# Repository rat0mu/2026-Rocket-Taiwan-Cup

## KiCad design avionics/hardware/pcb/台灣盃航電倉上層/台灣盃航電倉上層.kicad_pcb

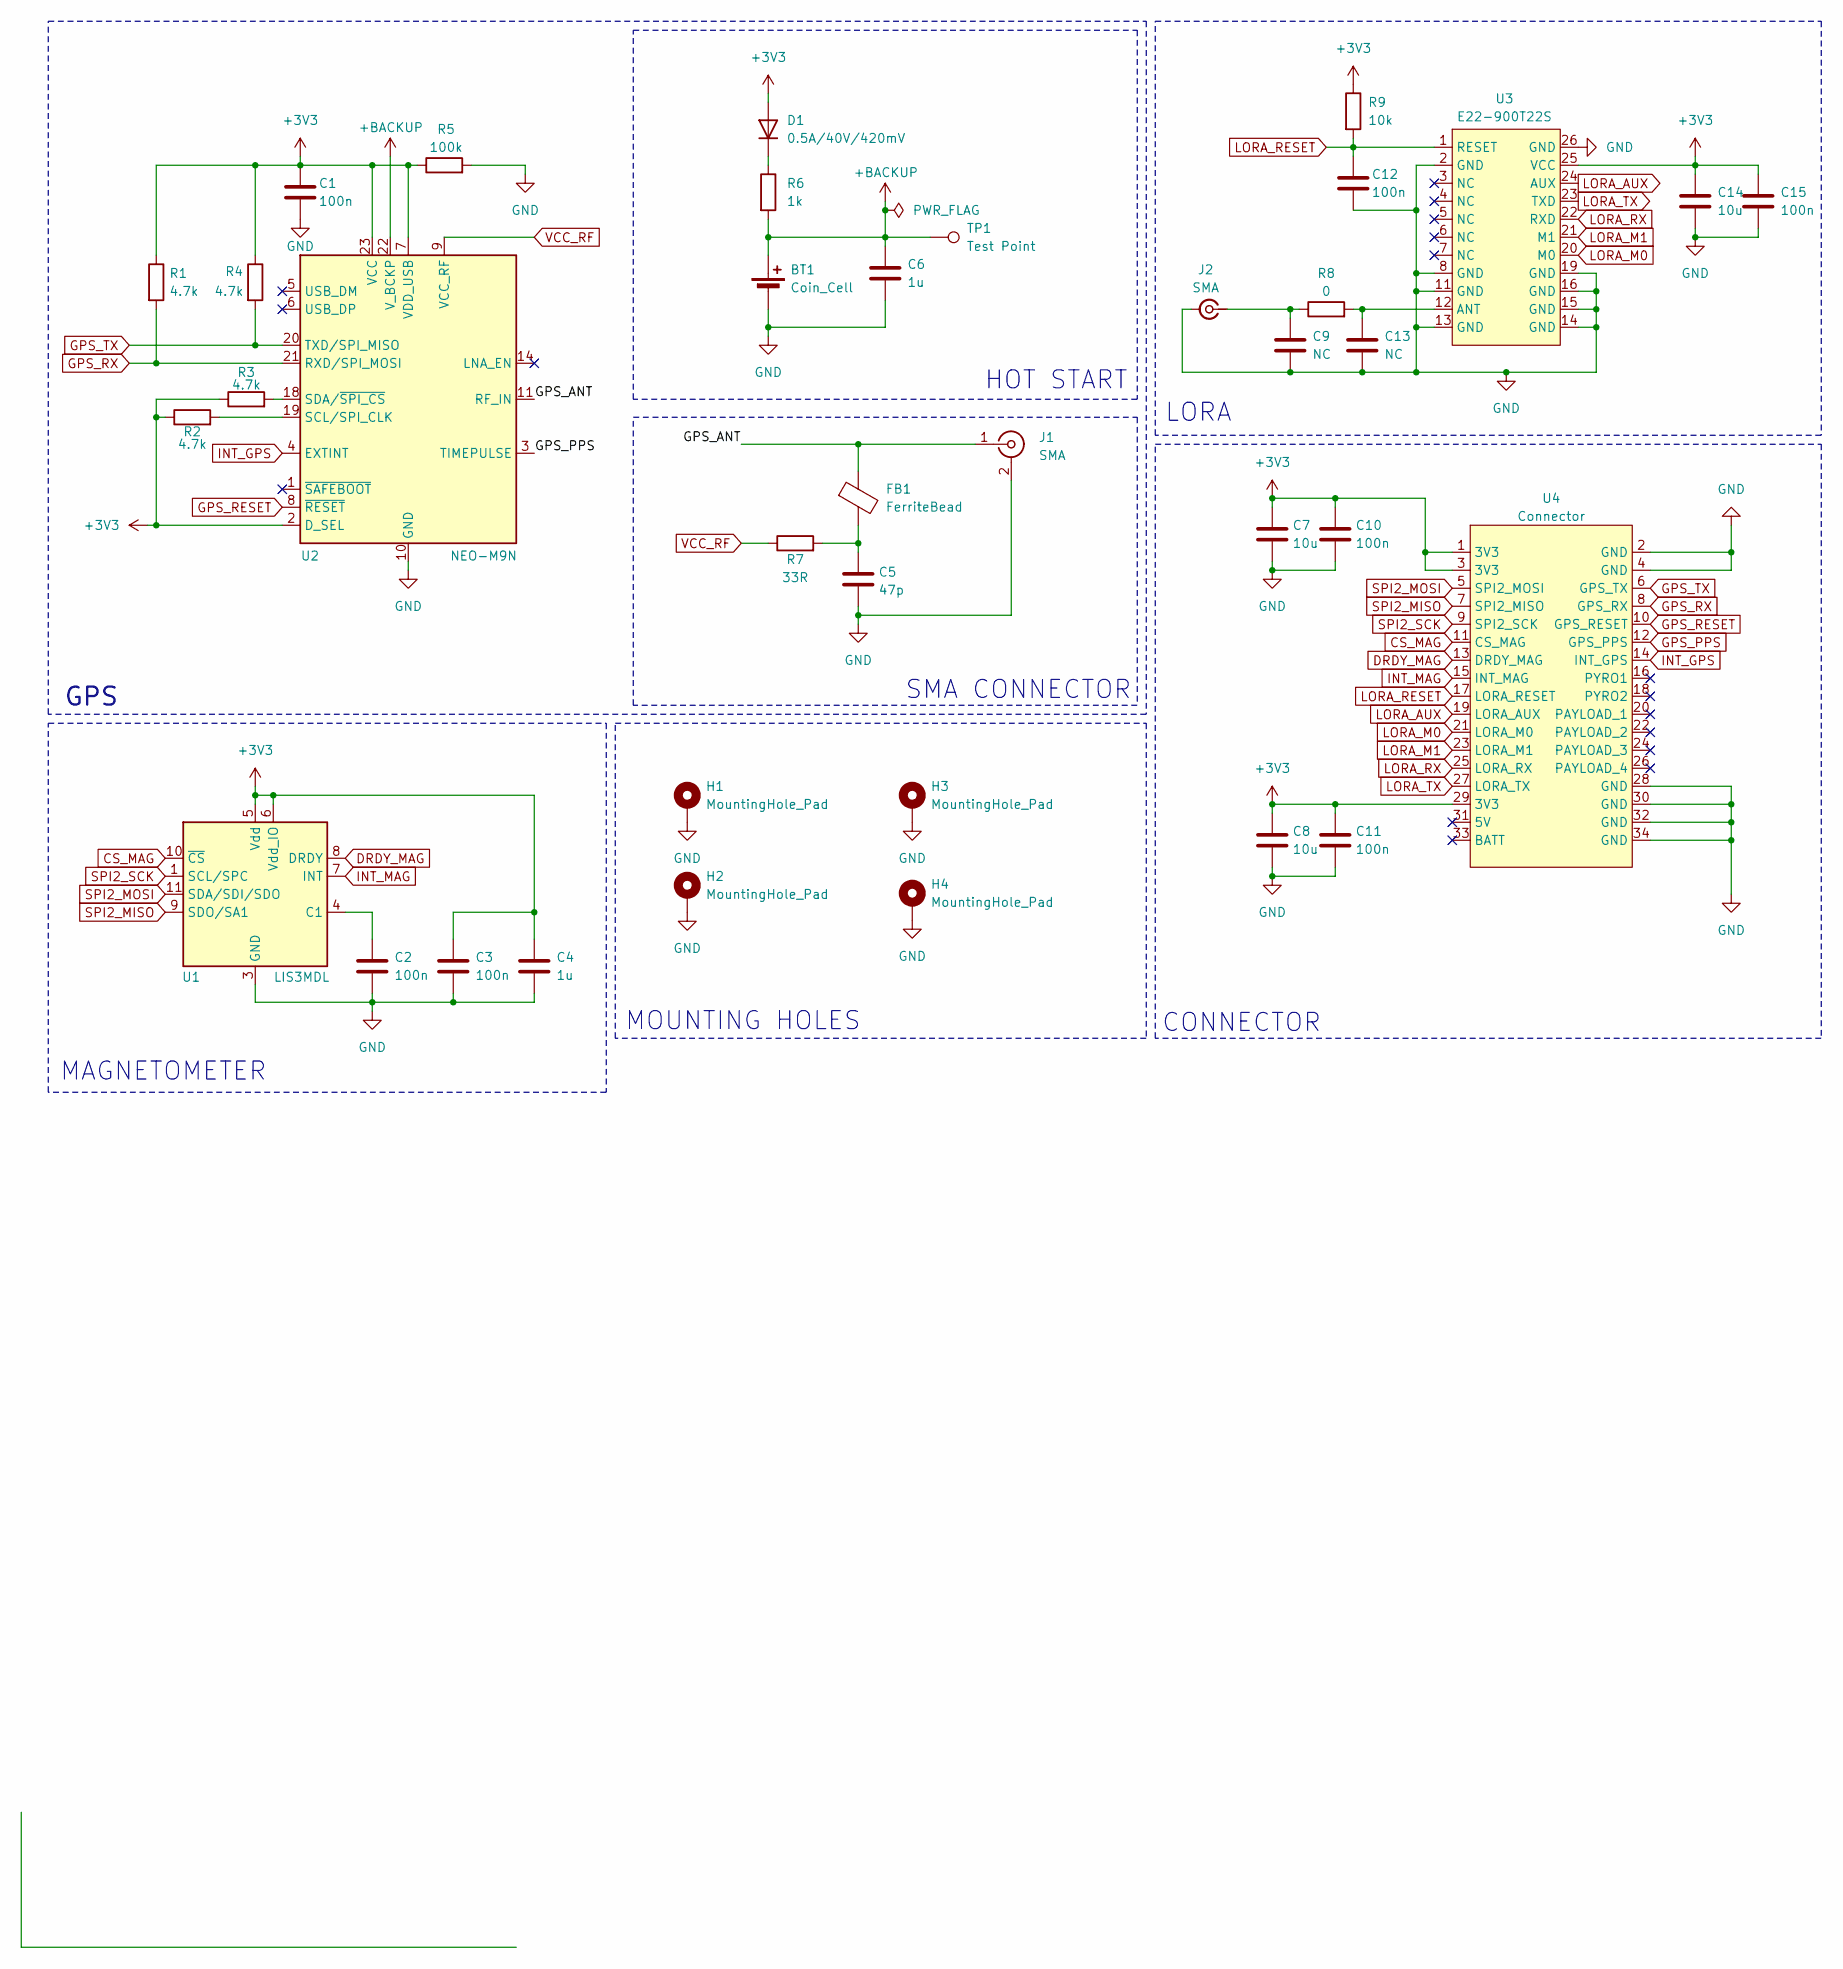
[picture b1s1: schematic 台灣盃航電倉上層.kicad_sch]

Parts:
BT1: Coin_Cell; BatteryHolder_Keystone_3000_1x12mm
C1: 100n; C_0201_0603Metric
C2, C3, C10, C11, C12, C15: 100n; C_0603_1608Metric
C4: 1u; C_0603_1608Metric
C5: 47p; C_0201_0603Metric
C6: 1u; C_0201_0603Metric
C7, C8, C14: 10u; C_0805_2012Metric
C9, C13: NC; C_0402_1005Metric
D1: 0.5A/40V/420mV; D_SOD-123
FB1: FerriteBead; L_0603_1608Metric
H1, H2, H3, H4: MountingHole_Pad; MountingHole_2.2mm_M2_DIN965_Pad
J1, J2: SMA; SMA_Amphenol_132134-10_Vertical
R1, R2, R3, R4: 4.7k; R_0603_1608Metric
R5: 100k; R_0603_1608Metric
R6: 1k; R_0603_1608Metric
R7: 33R; R_0603_1608Metric
R8: 0; R_0402_1005Metric
R9: 10k; R_0603_1608Metric
TP1: Test Point; TestPoint_Pad_1.0x1.0mm
U1: LIS3MDL; LGA-12_2x2mm_P0.5mm
U2: NEO-M9N; ublox_NEO
U3: E22-900T22S
U4: Connector; PinSocket_2x17_P2.54mm_Vertical

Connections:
+3V3: C1.1, C3.1, C4.1, C7.1, C8.1, C10.1, C11.1, C14.1, C15.1, D1.2 (A), R1.1, R2.1, R3.1, R4.1, R5.1, R9.1, U1.5 (Vdd), U1.6 (Vdd_IO), U2.2 (D_SEL), U2.7 (VDD_USB), U2.23 (VCC), U3.25 (VCC), U4.1 (3V3), U4.3 (3V3), U4.29 (3V3)
+BACKUP: BT1.1 (+), C6.1, R6.2, TP1.1, U2.22 (V_BCKP)
/GPS_ANT: FB1.1, J1.1 (In), U2.11 (RF_IN)
CS_MAG: U1.10 (~CS), U4.11 (CS_MAG)
DRDY_MAG: U1.8 (DRDY), U4.13 (DRDY_MAG)
GND: BT1.2 (-), C1.2, C2.2, C3.2, C4.2, C5.2, C6.2, C7.2, C8.2, C9.2, C10.2, C11.2, C12.2, C13.2, C14.2, C15.2, H1.1, H2.1, H3.1, H4.1, J1.2 (Ext), J2.2 (Ext), R5.2, U1.2 (GND), U1.3 (GND), U1.12 (GND), U2.10 (GND), U2.12 (GND), U2.13 (GND), U2.24 (GND), U3.2 (GND), U3.8 (GND), U3.11 (GND), U3.13 (GND), U3.14 (GND), U3.15 (GND), U3.16 (GND), U3.19 (GND), U3.26 (GND), U4.2 (GND), U4.4 (GND), U4.28 (GND), U4.30 (GND), U4.32 (GND), U4.34 (GND)
GPS_PPS: U2.3 (TIMEPULSE), U4.12 (GPS_PPS)
GPS_RESET: U2.8 (~RESET), U4.10 (GPS_RESET)
GPS_RX: R1.2, U2.21 (RXD/SPI_MOSI), U4.8 (GPS_RX)
GPS_TX: R4.2, U2.20 (TXD/SPI_MISO), U4.6 (GPS_TX)
INT_GPS: U2.4 (EXTINT), U4.14 (INT_GPS)
INT_MAG: U1.7 (INT), U4.15 (INT_MAG)
LORA_AUX: U3.24 (AUX), U4.19 (LORA_AUX)
LORA_M0: U3.20 (M0), U4.21 (LORA_M0)
LORA_M1: U3.21 (M1), U4.23 (LORA_M1)
LORA_RESET: C12.1, R9.2, U3.1 (RESET), U4.17 (LORA_RESET)
LORA_RX: U3.22 (RXD), U4.25 (LORA_RX)
LORA_TX: U3.23 (TXD), U4.27 (LORA_TX)
unnamed: C5.1, FB1.2, R7.2
unnamed: D1.1 (K), R6.1
unnamed: C9.1, J2.1 (In), R8.1
unnamed: C2.1, U1.4 (C1)
unnamed: R2.2, U2.19 (SCL/SPI_CLK)
unnamed: R3.2, U2.18 (SDA/~SPI_CS)
unnamed: C13.1, R8.2, U3.12 (ANT)
SPI2_MISO: U1.9 (SDO/SA1), U4.7 (SPI2_MISO)
SPI2_MOSI: U1.11 (SDA/SDI/SDO), U4.5 (SPI2_MOSI)
SPI2_SCK: U1.1 (SCL/SPC), U4.9 (SPI2_SCK)
VCC_RF: R7.1, U2.9 (VCC_RF)

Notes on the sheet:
HOT START
MAGNETOMETER
GPS
MOUNTING HOLES
LORA
SMA CONNECTOR
CONNECTOR

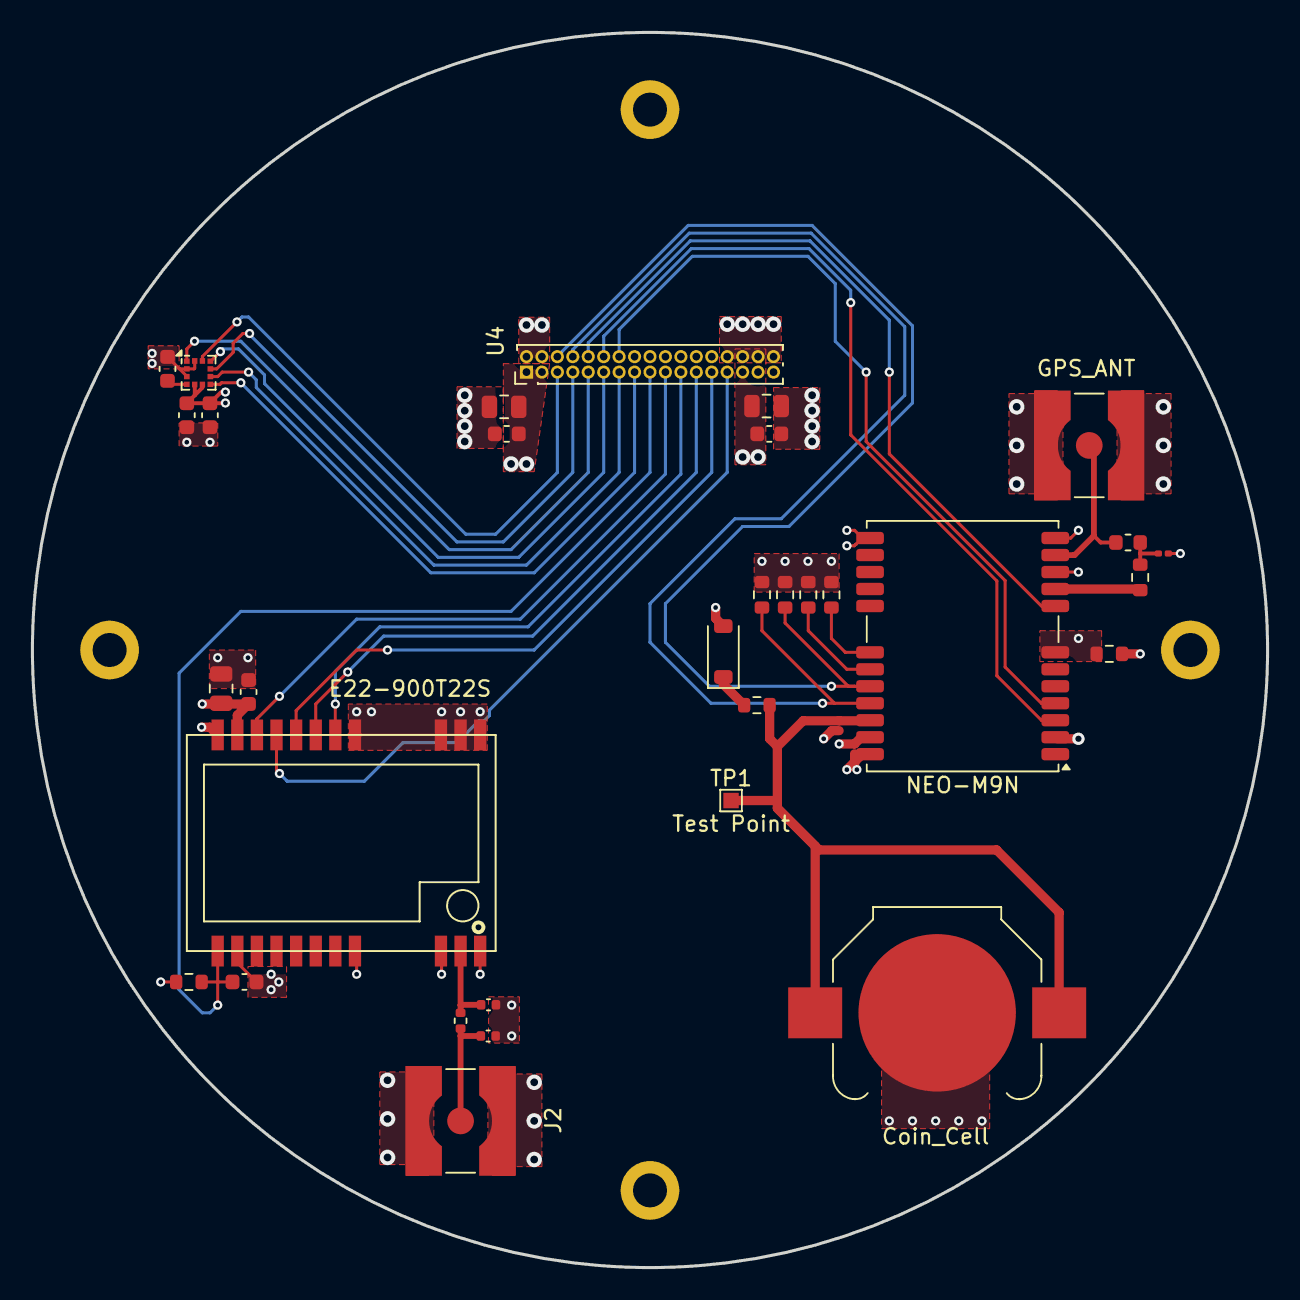
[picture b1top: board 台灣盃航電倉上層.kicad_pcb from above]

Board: 4 copper layers, 80.0 x 80.0 mm, 38 parts (0 on the bottom side), 29 nets.

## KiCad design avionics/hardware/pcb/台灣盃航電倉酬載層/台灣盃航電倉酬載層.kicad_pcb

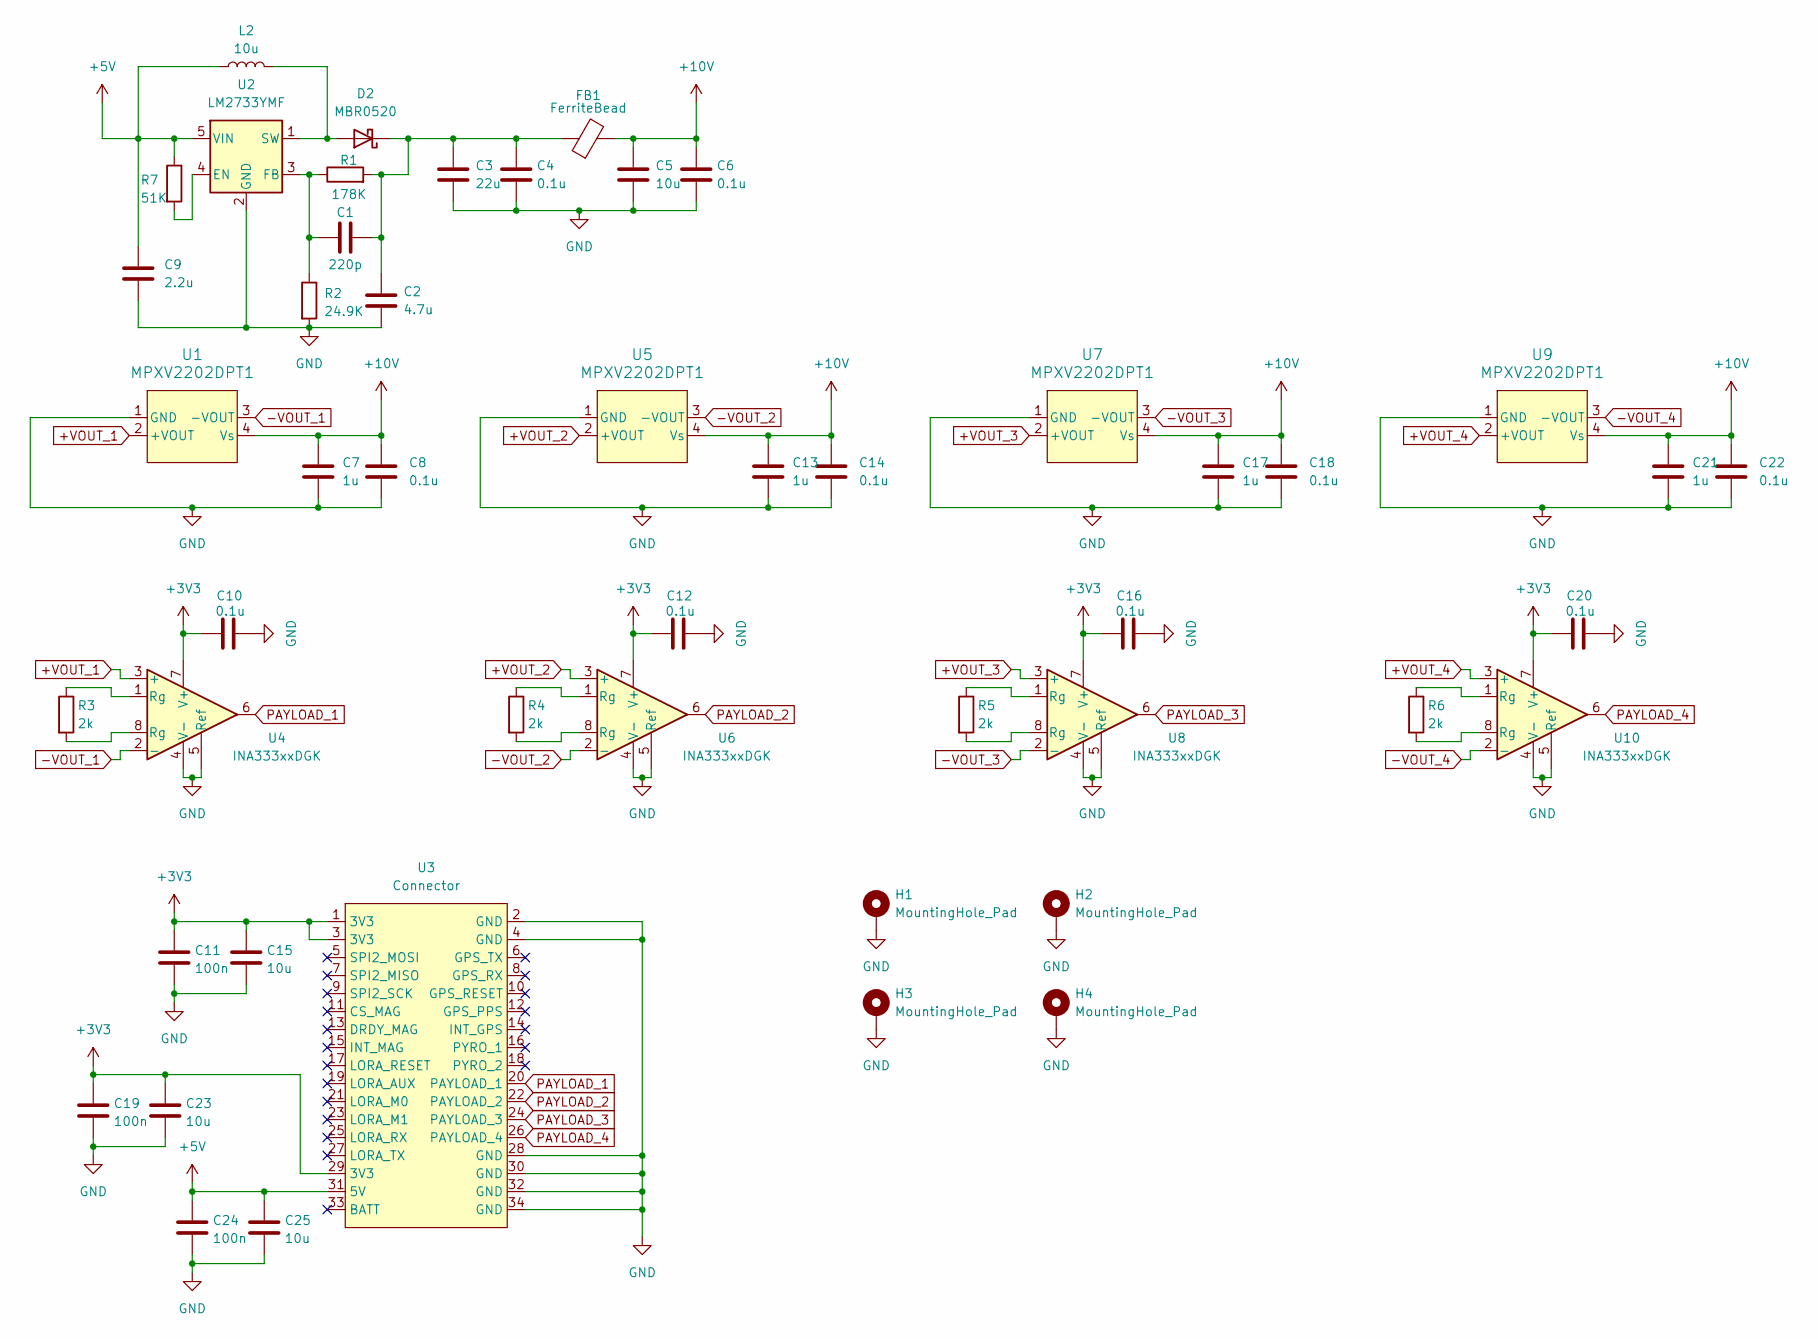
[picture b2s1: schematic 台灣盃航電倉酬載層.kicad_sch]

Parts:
C1: 220p; C_0402_1005Metric
C2: 4.7u; C_0603_1608Metric
C3: 22u; C_0805_2012Metric
C4, C6, C8, C10, C12, C14, C16, C18, C20, C22: 0.1u; C_0402_1005Metric
C5, C15, C23, C25: 10u; C_0603_1608Metric
C7, C13, C17, C21: 1u; C_0402_1005Metric
C9: 2.2u; C_0603_1608Metric
C11, C19, C24: 100n; C_0402_1005Metric
D2: MBR0520; D_SOD-123
FB1: FerriteBead; L_0603_1608Metric
H1, H2, H3, H4: MountingHole_Pad; MountingHole_2.2mm_M2_DIN965_Pad
L2: 10u; L_1206_3216Metric
R1: 178K; R_0603_1608Metric
R2: 24.9K; R_0603_1608Metric
R3, R4, R5, R6: 2k; R_0603_1608Metric
R7: 51K; R_0603_1608Metric
U1, U5, U7, U9: MPXV2202DPT1; XDCR_MPXV2202DPT1
U2: LM2733YMF; SOT-23-5
U3: Connector; PinHeader_2x17_P1.00mm_Vertical
U4, U6, U8, U10: INA333xxDGK; VSSOP-8_3x3mm_P0.65mm

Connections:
+3V3: C10.1, C11.1, C12.1, C15.1, C16.1, C19.1, C20.1, C23.1, U3.1 (3V3), U3.3 (3V3), U3.29 (3V3), U4.7 (V+), U6.7 (V+), U8.7 (V+), U10.7 (V+)
+5V: C9.1, C24.1, C25.1, L2.1, R7.1, U2.5 (VIN), U3.31 (5V)
+10V: C5.1, C6.1, C7.1, C8.1, C13.1, C14.1, C17.1, C18.1, C21.1, C22.1, FB1.2, U1.4 (Vs), U5.4 (Vs), U7.4 (Vs), U9.4 (Vs)
+VOUT_1: U1.2 (+VOUT), U4.3 (+)
+VOUT_2: U5.2 (+VOUT), U6.3 (+)
+VOUT_3: U7.2 (+VOUT), U8.3 (+)
+VOUT_4: U9.2 (+VOUT), U10.3 (+)
-VOUT_1: U1.3 (-VOUT), U4.2 (-)
-VOUT_2: U5.3 (-VOUT), U6.2 (-)
-VOUT_3: U7.3 (-VOUT), U8.2 (-)
-VOUT_4: U9.3 (-VOUT), U10.2 (-)
GND: C2.2, C3.2, C4.2, C5.2, C6.2, C7.2, C8.2, C9.2, C10.2, C11.2, C12.2, C13.2, C14.2, C15.2, C16.2, C17.2, C18.2, C19.2, C20.2, C21.2, C22.2, C23.2, C24.2, C25.2, H1.1, H2.1, H3.1, H4.1, R2.2, U1.1 (GND), U2.2 (GND), U3.2 (GND), U3.4 (GND), U3.28 (GND), U3.30 (GND), U3.32 (GND), U3.34 (GND), U4.4 (V-), U4.5 (Ref), U5.1 (GND), U6.4 (V-), U6.5 (Ref), U7.1 (GND), U8.4 (V-), U8.5 (Ref), U9.1 (GND), U10.4 (V-), U10.5 (Ref)
unnamed: D2.2 (A), L2.2, U2.1 (SW)
unnamed: C1.2, C2.1, C3.1, C4.1, D2.1 (K), FB1.1, R1.2
unnamed: R3.1, U4.1 (Rg)
unnamed: R3.2, U4.8 (Rg)
unnamed: R4.1, U6.1 (Rg)
unnamed: R4.2, U6.8 (Rg)
unnamed: R5.1, U8.1 (Rg)
unnamed: R5.2, U8.8 (Rg)
unnamed: R6.1, U10.1 (Rg)
unnamed: R6.2, U10.8 (Rg)
unnamed: R7.2, U2.4 (EN)
unnamed: C1.1, R1.1, R2.1, U2.3 (FB)
PAYLOAD_1: U3.20 (PAYLOAD_1), U4.6
PAYLOAD_2: U3.22 (PAYLOAD_2), U6.6
PAYLOAD_3: U3.24 (PAYLOAD_3), U8.6
PAYLOAD_4: U3.26 (PAYLOAD_4), U10.6

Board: 2 copper layers, 49 parts (0 on the bottom side), 28 nets, no tracks yet.
